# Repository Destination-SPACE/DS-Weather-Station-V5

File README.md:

<div align="center">
    
    <h1>Destination Weather Station v5</h1>
    <p>An Open Source In-Situ Sensing Platform Compatible with Adafruit Feather and SparkFun Thing platforms</p>
</div>

## 🌟 About the Project
Destination Weather Station is the the latest version of remote sensing tools developed to teach students across the southeastern United States about climate science and remote sensing.

## 📝 Specifications
This kit includes all the necessary components to get started with the Destination Weather Station v5. The weather station consists of the following

### 🤖 Microcontroller
- Adafruit ESP32-S3 Reverse TFT Feather
### 💾 Storage
- Ejectable microSD card socket
- 2-Kbit EEPROM
### ⚡ Power
- 2-pin JST-PH connector for 1s Lithium Polymer Ion batteries and charger
- SPDT slide switch
- 50mAh LiPo battery
### 🌡️ Sensors
- Bosch BME280 environmental sensor
### 👤 User Interface
- 240x135px color TFT display
- 3x programmable buttons
- STEMMA QT expansion sensor connector
## ⚙️ Hardware
All hardware files can be found [here](hardware)
## 💻 Firmware
All program files can be found [here](software)
## 🗂️ Documentation
Documentation for the weather station can be found [here](docs)

## Licenses
Each of the above sections are individually licensed. Terms and conditions apply within their respective folders.

**Documentation - [Apache License 2.0](docs/LICENSE)** <br>
**Hardware - [CERN-OHL-P](hardware/LICENSE)** <br>
**Firmware - [The MIT License](firmware/LICENSE)**

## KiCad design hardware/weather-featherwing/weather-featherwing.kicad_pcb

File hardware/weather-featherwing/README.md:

# Weather FeatherWing v1.2 Hardware
KiCad files for the Weather FeatherWing v1.2

## KiCanvas
View schematic and PCB files with [KiCanvas](https://kicanvas.org/?github=https%3A%2F%2Fgithub.com%2FDestination-SPACE%2FDS-Weather-Station-V5%2Ftree%2Fmain%2Fhardware%2Fweather-featherwing)

## Directory
### [🧾 Bill of Materials](bom/bom.md)
### [📄 Datasheets](datasheets)
### [📐 Gerbers](gerber)
### [📰 Schematics](pdf)

Licensed under [CERN-OHL-P](LICENSE)

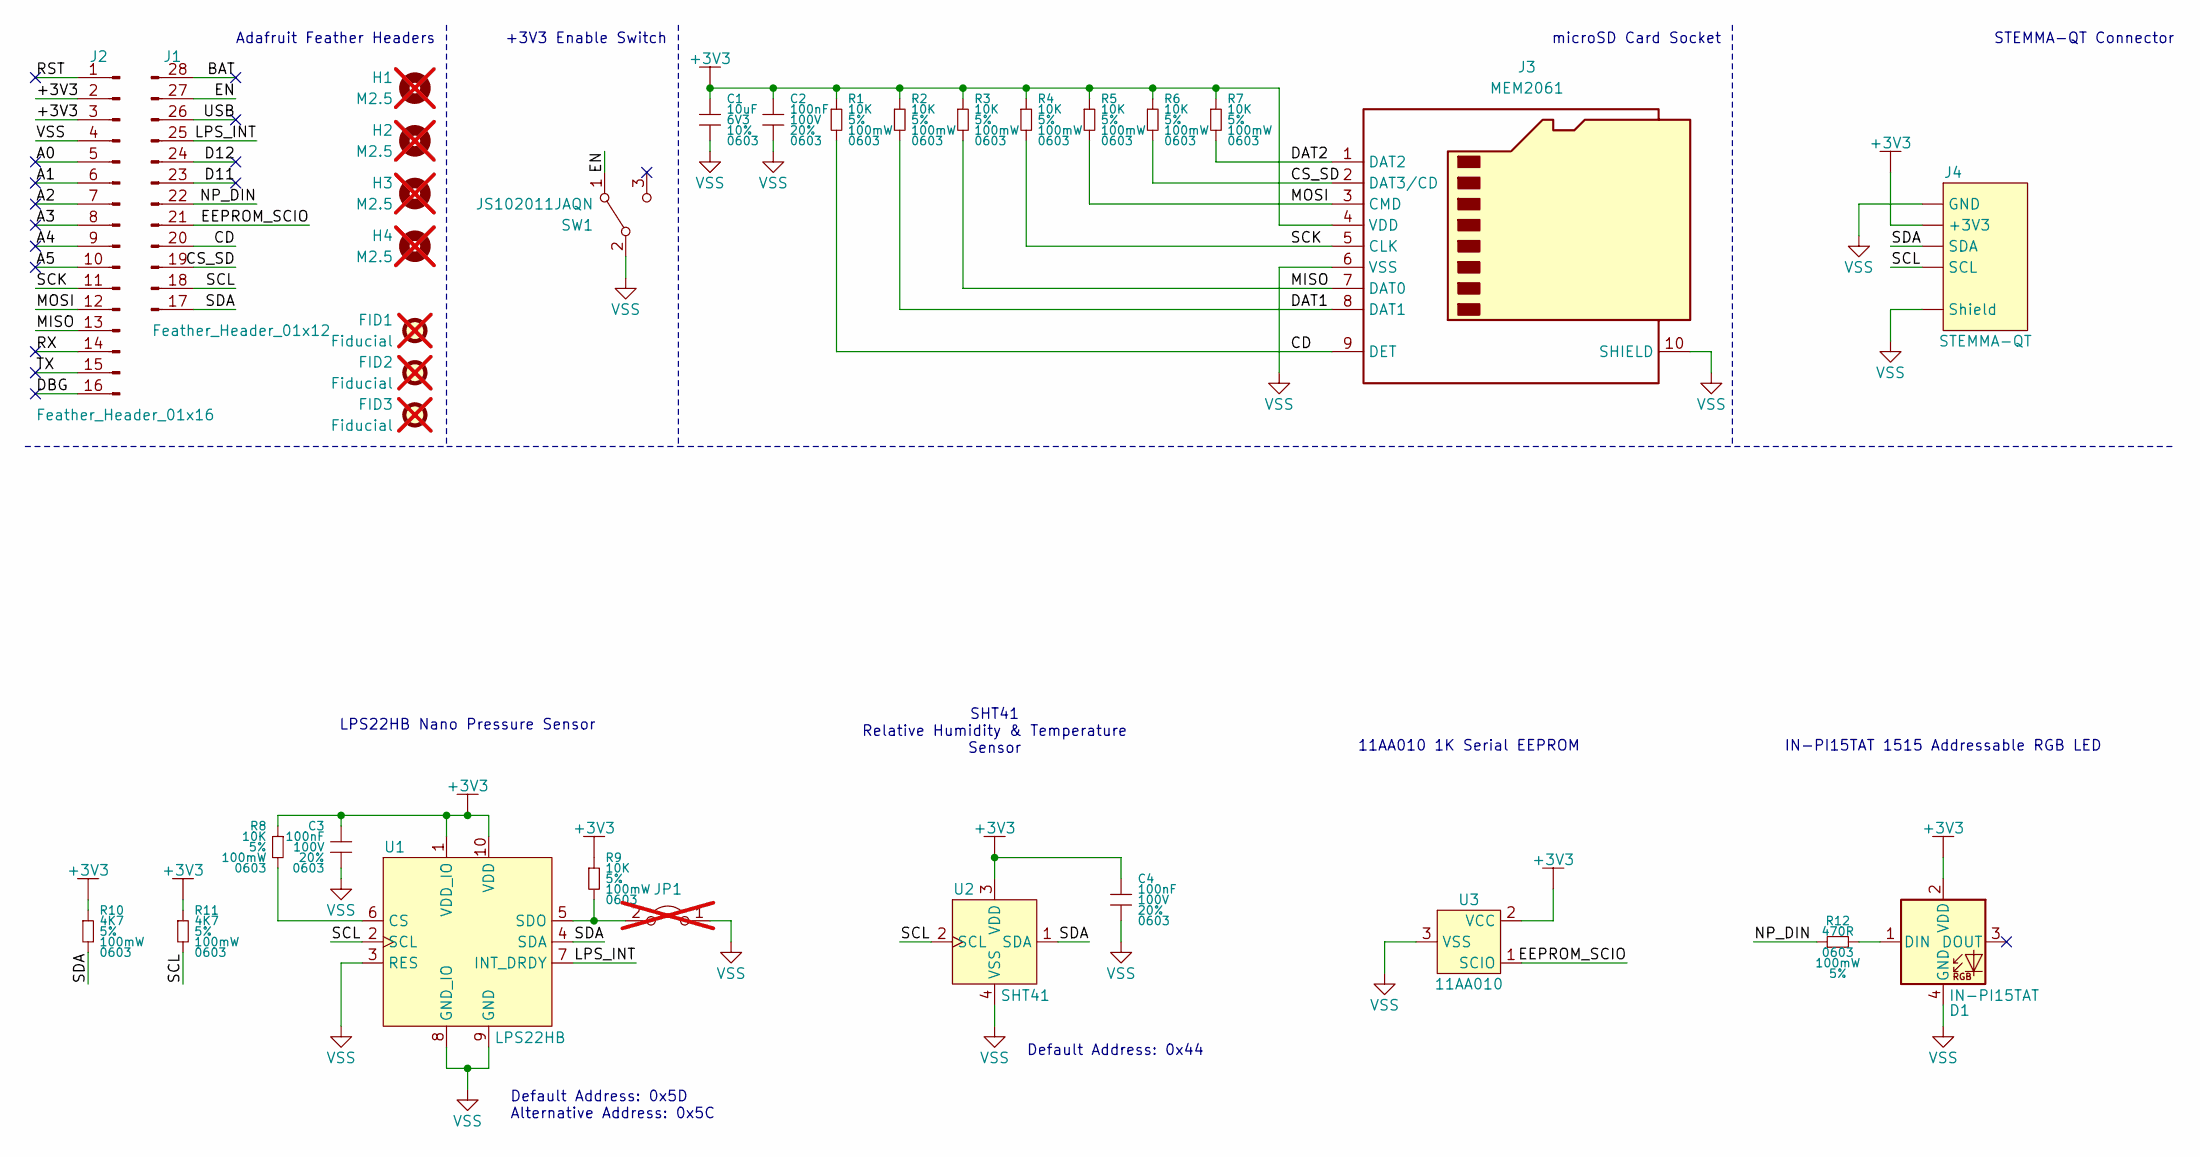
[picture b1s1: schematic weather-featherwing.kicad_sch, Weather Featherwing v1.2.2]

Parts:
C1: 10uF; GRT0603; Tolerance 10%; Voltage Rating 6V3; MPN GRM188R60J106KE47D
C2, C3, C4: 100nF; GRT0603; Tolerance 20%; Voltage Rating 100V; MPN GRM188R72A104MA35D
D1: IN-PI15TAT; IN-PI15TAT5R5G5B; MPN IN-PI15TAT5R5G5B
FID1, FID2, FID3: Fiducial; Fiducial_1mm_Mask2mm; not fitted
H1, H2: M2.5; M2.54_PTH; not fitted
H3, H4: M2.5; M2.54_NPTH; not fitted
J1: Feather_Header_01x12; conn_01x12_254; MPN PREC012SAAN-RC
J2: Feather_Header_01x16; conn_01x16_254; MPN PREC016SAAN-RC
J3: MEM2061; MPN MEM2061-01-188-00-A
J4: STEMMA-QT; JST_SH_SM04B-SRSS-TB; MPN SM04B-SRSS-TB
JP1: Jumper_2_Open; SolderJumper-2_P1.3mm_Open_TrianglePad1.0x1.5mm; not fitted
R1, R2, R3, R4, R5, R6, R7, R8, R9: 10K; CRCW0603; Tolerance 5%; Power Rating 100mW; MPN CRCW060310K0JNEA
R10, R11: 4K7; CRCW0603; Tolerance 5%; Power Rating 100mW; mpn CRCW06034K70JNEA
R12: 470R; CRCW0603; Tolerance 5%; Power Rating 100mW; mpn CRCW0603470RJNEB
SW1: JS102011JAQN; MPN JS102011JAQN
U1: LPS22HB; LPS22; mpn LPS22HBTR
U2: SHT41; SHT4x; MPN SHT41-AD1F-R2
U3: 11AA010; SOT95P237X112-3N; MPN 11AA010T-I/TT

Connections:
+3V3: C1.1, C2.1, C3.1, C4.1, D1.2 (VDD), J2.2, J2.3, J3.4 (VDD), J4.2 (+3V3), R1.1, R2.1, R3.1, R4.1, R5.1, R6.1, R7.1, R8.1, R9.1, R10.1, R11.1, U1.1 (VDD_IO), U1.10 (VDD), U2.3 (VDD), U3.2 (VCC)
/A0: J2.5
/A1: J2.6
/A2: J2.7
/A3: J2.8
/A4: J2.9
/A5: J2.10
/BAT: J1.28
/CD: J1.20, J3.9 (DET), R1.2
/CS_SD: J1.19, J3.2 (DAT3/CD), R6.2
/D11: J1.23 (3)
/D12: J1.24
/DAT1: J3.8 (DAT1), R2.2
/DAT2: J3.1 (DAT2), R7.2
/DBG: J2.16
/EEPROM_SCIO: J1.21, U3.1 (SCIO)
/EN: J1.27, SW1.1 (A)
/LPS_INT: J1.25, U1.7 (INT_DRDY)
/MISO: J2.13, J3.7 (DAT0), R3.2
/MOSI: J2.12, J3.3 (CMD), R5.2
/NP_DIN: J1.22, R12.1
/RST: J2.1
/RX: J2.14
/SCK: J2.11, J3.5 (CLK), R4.2
/SCL: J1.18, J4.4 (SCL), R11.2, U1.2 (SCL), U2.2 (SCL)
/SDA: J1.17, J4.3 (SDA), R10.2, U1.4 (SDA), U2.1 (SDA)
/TX: J2.15
/USB: J1.26
unnamed: D1.1 (DIN), R12.2
unnamed: JP1.2 (B), R9.2, U1.5 (SDO)
unnamed: R8.2, U1.6 (CS)
VSS: C1.2, C2.2, C3.2, C4.2, D1.4 (GND), J2.4, J3.6 (VSS), J3.10 (SHIELD), J4.1 (GND), J4.MP (Shield), JP1.1 (A), SW1.2 (B), U1.3 (RES), U1.8 (GND_IO), U1.9 (GND), U2.4 (VSS), U3.3 (VSS)

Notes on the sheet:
STEMMA-QT Connector
Adafruit Feather Headers
microSD Card Socket
+3V3 Enable Switch
Default Address: 0x44
Default Address: 0x5D Alternative Address: 0x5C
IN-PI15TAT 1515 Addressable RGB LED
11AA010 1K Serial EEPROM
SHT41 Relative Humidity & Temperature Sensor
LPS22HB Nano Pressure Sensor

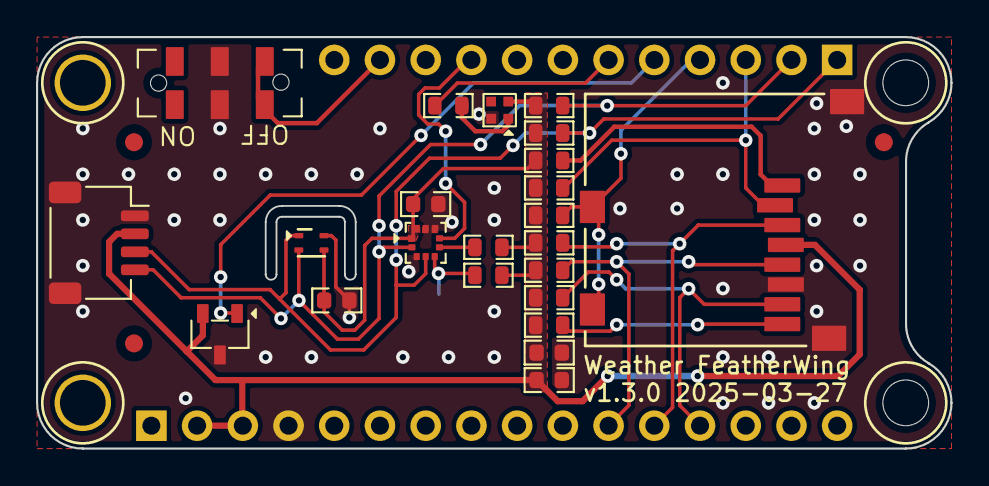
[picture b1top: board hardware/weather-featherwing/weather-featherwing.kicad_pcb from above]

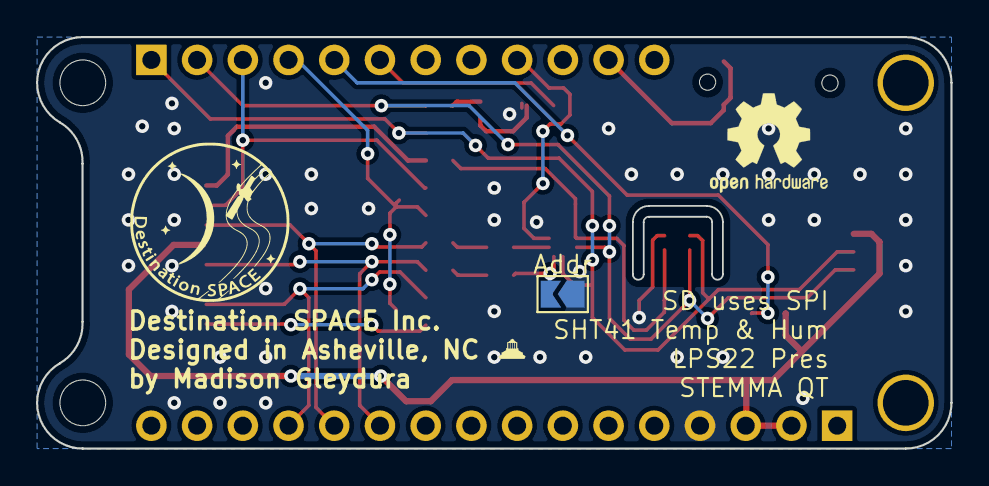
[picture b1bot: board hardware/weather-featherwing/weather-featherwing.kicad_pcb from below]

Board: 2 copper layers, 50.8 x 22.9 mm, 33 parts (3 on the bottom side), 18 nets.

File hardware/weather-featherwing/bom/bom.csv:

Item,Qty,Reference(s),Value,Datasheet,Manufacturer,mpn,Package
1,1,C1,10uF,datasheets/AVX-CX5R-KGM-MLCC.pdf,KYOCERA AVX,KGM15CR50J106MT,0603
2,3,"C2, C3, C4",100nF,datasheets/AVX-CX5R-KGM-MLCC.pdf,KYOCERA AVX,KGM15AR51H104KT,0603
3,9,"R1, R2, R3, R4, R5, R6, R7, R10, R11",10K,datasheets/Vishay-Dale-DCRCWe3.pdf,Vishay Dale,CRCW060310K0JNEB,0603
4,2,"R8, R9",4K7,datasheets/Vishay-Dale-DCRCWe3.pdf,Vishay Dale,CRCW06034K70JNEA,0603
5,1,R12,470R,datasheets/Vishay-Dale-DCRCWe3.pdf,Vishay Dale,CRCW0603470RJNEB,0603
6,1,D1,IN-PI15TAT,datasheets/IN-PI15TAT5R5G5B.pdf,Inolux,IN-PI15TAT5R5G5B,15x15
7,1,J1,Feather_Header_01x16,datasheets/Sullins-xxxCxxxSxxN-RC.pdf,Sullins Connector Solutions,PREC016SAAN-RC,2.54mm
8,1,J2,Feather_Header_01x12,datasheets/Sullins-xxxCxxxSxxN-RC.pdf,Sullins Connector Solutions,PREC012SAAN-RC,2.54mm
9,1,J3,MEM2061,datasheets/GCT-MEM2061.pdf,GCT,MEM2061-01-188-00-A,N/A
20,1,J4,STEMMA-QT,datasheets/JST-eSH.pdf,JST Sales America Inc.,SM04B-SRSS-TB,JST-SH
11,1,SW1,JS102011SAQN,datasheets/CK-JS-SERIES.pdf,C&K,JS102011SAQN,N/A
12,1,U1,LPS22HB,datasheets/ST-LPS22HB.pdf,STMicroelectronics,LPS22HBTR,HLGA
13,1,U2,SHT41,datasheets/Sensirion-SHT4x.pdf,Sensirion,SHT41-AD1B-R3,WDFN
14,1,U3,11AA010,datasheets/Microchip-11AAxxx_11LCxxx.pdf,Microchip,11AA010T-I/TT,SOT23

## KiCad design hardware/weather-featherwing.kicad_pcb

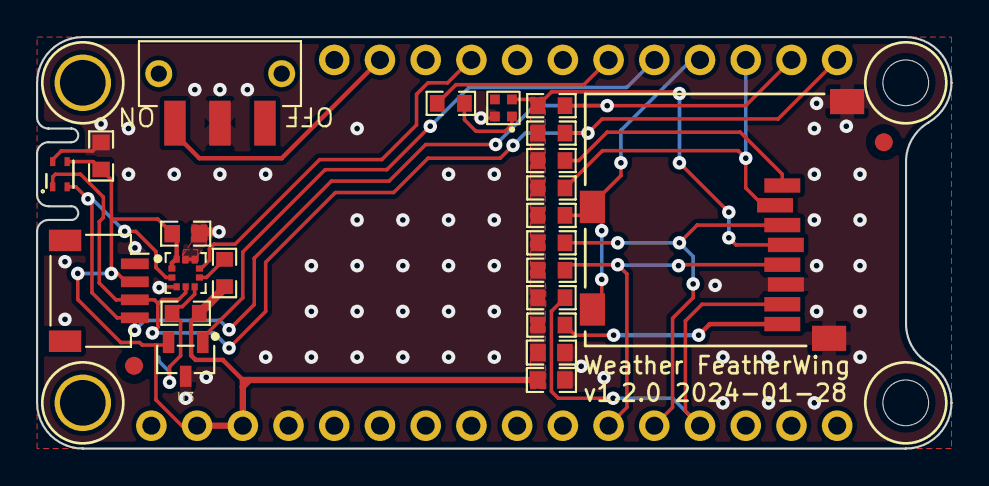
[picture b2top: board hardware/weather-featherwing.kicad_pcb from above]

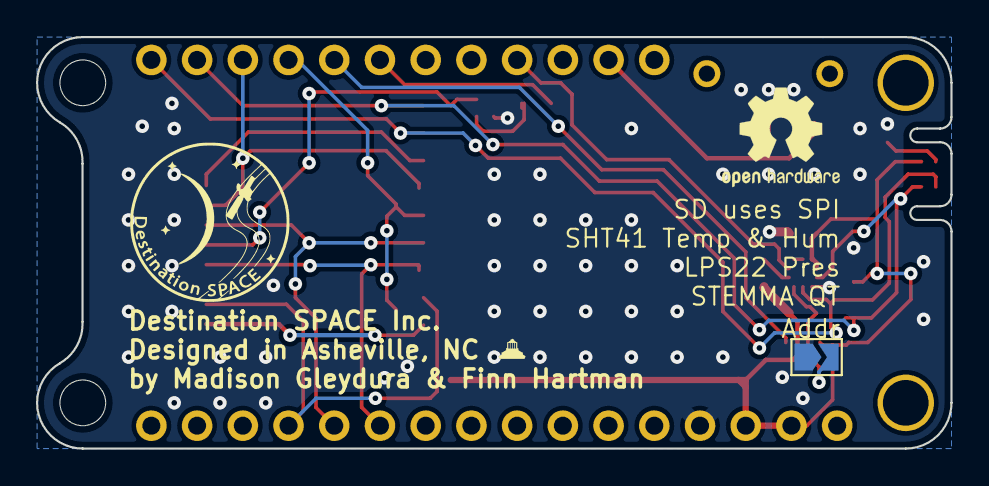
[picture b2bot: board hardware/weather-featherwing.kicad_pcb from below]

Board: 2 copper layers, 50.8 x 22.9 mm, 32 parts (3 on the bottom side), 18 nets.

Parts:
C1: 10uF; CAPC160X80X88L35N
C2, C3, C4: 100nF; CAPC160X80X88L35N
D1: IN-PI15TAT; IN-PI15TAT5R5G5B
FID1, FID2: Fiducial; Fiducial_1mm_Mask2mm
H1, H2: M2.5; M2.54_PTH
H3, H4: M2.5; M2.54_NPTH
J1: Feather_Header_01x16; conn_01x16_254
J2: Feather_Header_01x12; conn_01x12_254
J3: MEM2061
J4: STEMMA-QT; JST_SH_SM04B-SRSS-TB
JP1: Jumper_2_Open; SolderJumper-2_P1.3mm_Open_TrianglePad1.0x1.5mm
R1, R2, R3, R4, R5, R6, R7, R10, R11: 10K; RESC160X80X55L30N
R8, R9: 4K7; RESC160X80X55L30N
R12: 470R; RESC160X80X55L30N
SW1: JS102011SAQN
U1: LPS22HB; PQFN10P50_200X200X80L27X25N
U2: SHT41; SHT4x
U3: 11AA010; SOT95P237X112-3N

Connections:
+3V3: C1.1, C2.1, C3.1, C4.1, D1.2 (VDD), J1.2, J1.3, J3.4 (VDD), J4.2 (+3V3), R1.1, R2.1, R3.1, R4.1, R5.1, R6.1, R7.1, R8.1, R9.1, R10.1, R11.1, U1.1 (VDD_IO), U1.10 (VDD), U2.3 (VDD), U3.2 (VCC)
/CD: J2.20, J3.9 (DET), R1.2
/CS_SD: J2.19, J3.2 (DAT3/CD), R6.2
/DAT1: J3.8 (DAT1), R2.2
/DAT2: J3.1 (DAT2), R7.2
/EEPROM_SCIO: J2.21, U3.1 (SCIO)
/EN: J2.27, SW1.3 (C)
/LPS_INT: J2.25, U1.7 (INT_DRDY)
/MISO: J1.13, J3.7 (DAT0), R3.2
/MOSI: J1.12, J3.3 (CMD), R5.2
/NP_DIN: J2.22, R12.1
/SCK: J1.11, J3.5 (CLK), R4.2
/SCL: J2.18, R9.2, U1.2 (SCL), U2.2 (SCL)
/SDA: J2.17, R8.2, U1.4 (SDA), U2.1 (SDA)
GND: C1.2, C2.2, C3.2, C4.2, D1.4 (GND), J1.4, J3.6 (VSS), J3.10 (SHIELD), JP1.1 (A), SW1.2 (B), U1.3 (RES), U1.8 (GND_IO), U1.9 (GND), U2.4 (VSS), U3.3 (VSS)
unnamed: D1.1 (DIN), R12.2
unnamed: JP1.2 (B), R11.2, U1.5 (SDO)
unnamed: R10.2, U1.6 (CS)

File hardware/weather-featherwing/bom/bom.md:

# Bill of Materials
*Note: Some parts may be replaced with suitable alternatives

| Item | Qty | Reference | Value | Datasheet | Manufacturer | Manufacturer Part Number | Package |
|-----:|----:|:---------:|:-----:|:----------|:-------------|:-------------------------|--------:|
| 1 | 1 | C1 | 10uF | [AVX-CX5R-KGM](../datasheets/AVX-CX5R-KGM-MLCC.pdf) | KYOCERA AVX | KGM15CR50J106MT | 0603 |
| 2 | 3 | C2, C3, C4 | 0.1uF | [AVX-CX5R-KGM](../datasheets/AVX-CX5R-KGM-MLCC.pdf) | KYOCERA AVX | KGM15AR51H104KT | 0603 | 
| 3 | 9 | R1, R2, R3, R4, R5, R6, R7, R10, R11| 10K | [D/CRCW e3](../datasheets/Vishay-Dale-DCRCWe3.pdf) | Vishay Dale | CRCW060310K0JNEB | 0603 |
| 4 | 2 | R8, R9 | 4K7 | [D/CRCW e3](../datasheets/Vishay-Dale-DCRCWe3.pdf) | Vishay Dale | CRCW06034K70JNEA | 0603 |
| 5 | 1 | R12 | 470R | [D/CRCW e3](../datasheets/Vishay-Dale-DCRCWe3.pdf) | Vishay Dale | CRCW0603470RJNEB | 0603 |
| 6 | 1 | D1 | IN-PI15TAT | [IN-PI15TAT5R5G5B](../datasheets/IN-PI15TAT5R5G5B) | Inolux | IN-PI15TAT5R5G5B | 15x15 |
| 7 | 1 | J1 | Feather_Header_01x16 | [Sullins-Headers](../datasheets/Sullins-Headers.pdf) | Sullins Connector Solutions | PREC016SAAN-RC | 2.54mm |
| 8 | 1 | J2 | Feather_Header_01x12 | [Sullins-Headers](../datasheets/Sullins-Headers.pdf) | Sullins Connector Solutions | PREC012SAAN-RC | 2.54mm |
| 9 | 1 | J3 | MEM2061 | [GCT-MEM2061](../datasheets/GCT-MEM2061.pdf) | GCT | MEM2061-01-188-00-A | N/A |
| 10 | 1 | J4 | STEMMA-QT | [JST-eSH](../datasheets/JST-eSH.pdf) | JST Sales America Inc. | SM04B-SRSS-TB | JST-SH |
| 11 | 1 | SW1 | JS102011SAQN | [CK-JS-Series](../datasheets/CK-JS-SERIES.pdf) | C&K | JS102011SAQN | N/A |
| 12 | 1 | U1 | LPS22HB | [ST-LPS22HB](../datasheets/ST-LPS22HB.pdf) | STMicroelectronics | LPS22HBTR | HLGA |
| 13 | 1 | U2 | SHT41 | [Sensirion-SHT4x](../datasheets/Sensirion-SHT4x.pdf) | Sensirion | SHT41-AD1B-R3 | WDFN | 
| 14 | 1 | U3 | 11AA010 | [Microchip-11AAxxx_11LCxxx](../datasheets/Microchip-11AAXXX-11LCXXX.pdf) | Microchip | 11AA010T-I/TT | SOT23 |

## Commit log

2023-12-16 added folders
2023-12-16 Initialized Programs
2023-12-16 added code for NeoPixels
2023-12-17 First draft of Sensor code for SHT41 and LPS22
2023-12-17 added MIT license agreement and header
2023-12-17 edited header
2023-12-17 added microSD read program
2023-12-17 started demo code. created config YAML file
2023-12-18 Lots of demo code stuff
2023-12-22 ghgh
2023-12-23 json
2023-12-24 finished sensor code & added calc and formulas
2024-01-11 trying to get sensors to work
2024-01-26 changes and calibration code
2024-01-26 eeprom lib
2024-01-28 added hardware
2024-01-30 Calibration code and readme
2024-01-30 added BATCH installer for VS Code and Linux instructions
2024-01-31 backups
2024-01-31 edited code
2024-02-08 edited demo code
2024-02-08 created WiFi_Test
2024-02-12 wifi test code
2024-02-12 something probably
2024-02-12 something
2024-02-15 creaded WiFi range test programs
2024-02-15 fixed wifi code
2024-02-19 backup
2024-02-19 fdsf
2024-02-19 1.2.1 changes
2024-02-21 added ground station files
2024-02-26 svg for silkscreen
2024-03-09 rev3 changes
2024-03-10 blender renders and cleaned up files
2024-03-11 fixed gitignore. deleted temp files
2024-03-11 housekeeping
2024-03-12 License stuff
2024-03-12 stuff
2024-03-13 sensor test
2024-03-17 minor changes
2024-03-17 put sensor, units, and parameters in structures
2024-03-17 fixed struct declarations
2024-03-23 test jig code
2024-03-28 moved to root
2024-03-28 organization
2024-03-28 added workspace file
2024-04-06 new gerbers
2024-04-06 fixed code
2024-04-08 spelling and fixed to be v5.0
2024-04-08 add markdown file support
2024-04-08 remove .gitignore
2024-04-08 add _build and public to .gitignore
2024-04-08 add markdown extension
2024-04-08 add words to library
2024-04-09 changed index to a MarkDown file
2024-04-10 fixed spelling
2024-04-10 powershell script
2024-04-10 changed destination
2024-04-10 get user name for destination
2024-04-10 destination
2024-04-10 fixed destination again
2024-04-10 fixed exec dir
2024-04-10 force install
2024-04-10 get rid of force
2024-04-10 test for admin
2024-04-10 removed admin check
2024-04-10 deleted extra spacing
2024-04-10 re-arranged variables
2024-04-10 removed vs code installer BAT script
2024-04-11 fixed stuff
2024-04-11 fixed neopixel
2024-04-18 broken YAML stuff :(
2024-05-04 fixed ini
2024-05-04 fixed timer
2024-05-05 json test script
2024-05-06 added print statements
2024-05-06 added line break
2024-05-07 can now read config.json
2024-05-07 fixed fahrenheit conversion
2024-05-07 deleted YAML stuff
2024-05-11 changes :p
2024-05-14 fixed ALS sensor readout and table formatting
2024-05-15 renamed stuff
2024-05-19 added bootloader binary
2024-05-19 duel core test
2024-05-19 changed file type
2024-05-19 sync dev branch to main
2024-06-11 sync
2024-06-12 added pinout diagram
2024-06-14 synced from dev main.cpp
2024-06-14 pio stuff
2024-06-14 added debug comments to TFT
2024-06-16 chip detect stuff
2024-06-16 fixed student name print out
2024-06-16 add balloon transmit code
2024-06-16 copied files from demo
2024-06-16 add server stuff for WiFi
2024-06-16 created balloon receiver
2024-06-16 receiver code
2024-06-16 fixed ini files
2024-06-17 added some upload details
2024-06-17 tried to add async sends
2024-06-17 fixed "file.open()" to not clash with ESPAsyncWebServer stuff
2024-06-17 changed transmitter SSID and fixed typo on pressure var
2024-06-17 added Adafruit ESP32-S3 Feather environment
2024-06-17 added Unexpected Maker ESP32-S3 board to environments
2024-06-17 added build flags
2024-06-18 verified works - DeepSpace
2024-06-18 fixed card detect
2024-06-19 added sensor example sketches
2024-06-19 changed temperature from F to C. expansion sensors are now opt in.
2024-07-07 folder name change
2024-07-07 rename folders
2024-07-07 WiFi test programs
2024-07-07 Transmitter/receiver code now works
2024-07-07 renumbered folders
2024-07-07 created project copies
2024-07-07 deleted originals
2024-07-07 fixed gitignores
2024-07-11 Add new directory
2024-07-16 Added support for UM FeatherS3
2024-07-16 changes to units
2024-12-13 fixing repo
2025-03-29 redid footprints
2025-03-29 replaced 3D models
2025-03-29 updated datasheets
2025-03-29 added worksheet to project
2025-03-29 updated schematic refs
2025-03-29 fixed layout
2025-03-29 updated symbols
2025-04-01 added Weather-FeatherWing submodule
2025-08-18 renamed software folder to firmware
2025-08-18 removed old GitLab file
2025-08-18 moved .gitignore to /hardware
2025-08-18 new .gitignore for root
2025-08-18 removed old word from spelling
2025-08-18 removed
2025-08-18 fix ignore
2025-08-18 something about cpp extensions
2025-08-25 moved old sketches and created 2 simple zephyr apps. still testing...
2025-08-27 fixed bme280 example
2025-08-27 moved esp32s3 conf and overlays to boards folder
2025-08-27 fixed build and flash example commands
2025-08-27 ignore words
2025-08-27 added command to activate Zephyr Python venv
2025-08-27 removed requirement to clone zephyr repo. use system default
2025-08-27 fixed to get west to init in the correct directory
2025-08-29 stuff for building
2025-08-29 added lvgl and mbedtls modules
2025-08-29 a few more examples for testing
2025-08-29 add littlefs module
2025-08-29 sd card test
2025-09-03 fixed file names
2025-09-03 created Hello World! example
2025-09-03 removed GPIO stuff. Done by default
2025-09-03 added zephyr/sys/printk header
2025-09-03 file associations
